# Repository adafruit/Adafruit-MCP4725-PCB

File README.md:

## Adafruit MCP4725 12-Bit DAC Breakout PCB
<a href="http://www.adafruit.com/products/935"><br/>
Click here to purchase one from the Adafruit shop</a>

This breakout board features the easy-to-use MCP4725 12-bit DAC. Control it via I2C and send it the value you want it to output, and the VOUT pin will have it. Great for audio / analog projects, such as when you can't use PWM but need a sine wave or adjustable bias point.

We break out the ADDR/A0 pin so you can connect two of these DACs on one I2C bus, just tie that pin of one high to keep it from conflicting. Also included is a 6-pin header, for use in a breadboard. Works with both 3.3V or 5V logic.

Some nice extras with this chip: for chips that have 3.4Mbps Fast Mode I2C (Arduino's don't) you can update the Vout at ~200 KHz. There's an EEPROM so if you write the output voltage, you can 'store it' so if the device is power cycled it will restore that voltage. The output voltage is rail-to-rail and proportional to the power pin so if you run it from 3.3V, the output range is 0-3.3V. If you run it from 5V the output range is 0-5V.

These are the Eagle CAD files for the Adafruit MCP4725 12-Bit DAC Breakout:
- https://www.adafruit.com/products/935

### License

Adafruit invests time and resources providing this open source design, please support Adafruit and open-source hardware by purchasing products from [Adafruit](https://www.adafruit.com)!

All text above must be included in any redistribution

Designed by Limor Fried/Ladyada for Adafruit Industries.
Creative Commons Attribution/Share-Alike, all text above must be included in any redistribution. 
See license.txt for additional information.

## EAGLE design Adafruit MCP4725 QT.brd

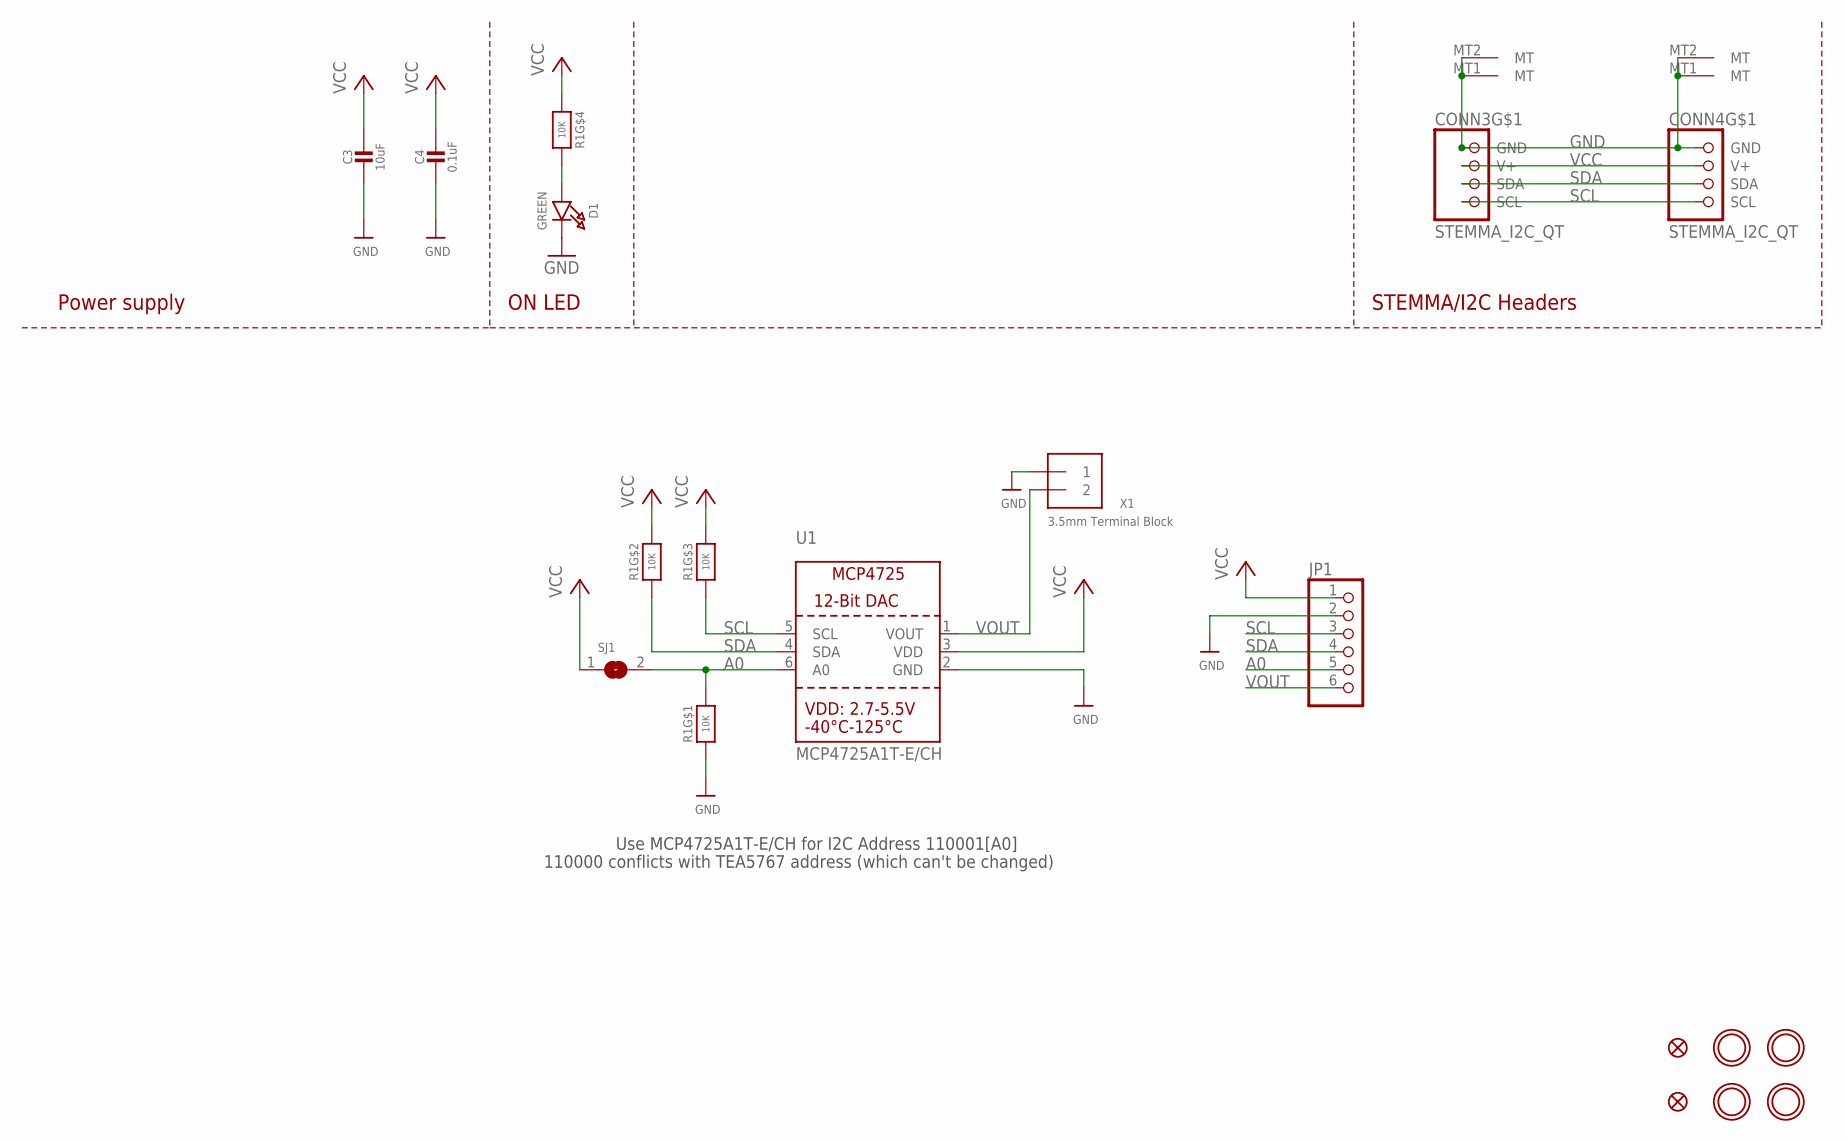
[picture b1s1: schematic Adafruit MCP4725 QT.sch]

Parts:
C3: 10uF; 0805-NO
C4: 0.1uF; 0603-NO
CONN3, CONN4: STEMMA_I2C_QT; JST_SH4
D1: GREEN; CHIPLED_0603_NOOUTLINE
FID3, FID4: FIDUCIAL_1MM
JP1: HEADER-1X670MIL; 1X06_ROUND_70
R1: 10K; RESPACK_4X0603
SJ1: SOLDERJUMPER; SOLDERJUMPER_ARROW_NOPASTE
U1: MCP4725A1T-E/CH; SOT23-6
U$20, U$21, U$25, U$27: MOUNTINGHOLE2.5; MOUNTINGHOLE_2.5_PLATED
X1: 3.5mm Terminal Block; TERMBLOCK_1X2-3.5MM

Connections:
A0: JP1.5, R1.8 (2), SJ1.2, U1.6 (A0)
GND: C3.2, C4.2, CONN3.1 (GND), CONN3.MT1 (MT), CONN3.MT2 (MT), CONN4.1 (GND), CONN4.MT1 (MT), CONN4.MT2 (MT), D1.C, JP1.2, R1.1, U1.2 (GND), X1.1
unnamed: D1.A, R1.5 (2)
SCL: CONN3.4 (SCL), CONN4.4 (SCL), JP1.3, R1.3 (1), U1.5 (SCL)
SDA: CONN3.3 (SDA), CONN4.3 (SDA), JP1.4, R1.2 (1), U1.4 (SDA)
VCC: C3.1, C4.1, CONN3.2 (V+), CONN4.2 (V+), JP1.1, R1.4 (1), R1.6 (2), R1.7 (2), SJ1.1, U1.3 (VDD)
VOUT: JP1.6, U1.1 (VOUT), X1.2

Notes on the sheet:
STEMMA/I2C Headers
ON LED
Power supply
Use MCP4725A1T-E/CH for I2C Address 110001[A0]
110000 conflicts with TEA5767 address (which can't be changed)

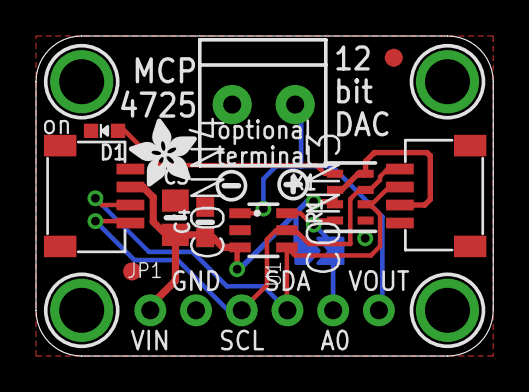
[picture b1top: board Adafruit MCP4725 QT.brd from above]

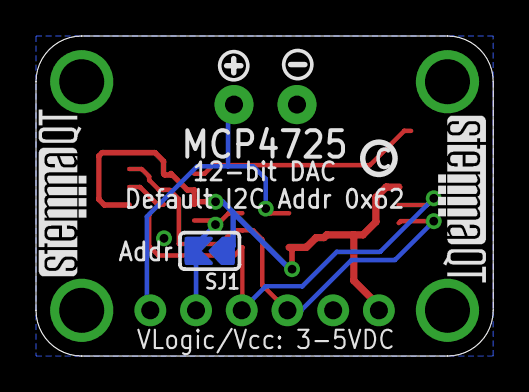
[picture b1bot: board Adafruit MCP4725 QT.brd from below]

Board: 2 copper layers, 25.4 x 17.8 mm, 24 parts (6 on the bottom side), 7 nets.

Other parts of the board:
U$2, U$7: SYMBOL_PLUS
U$4, U$5: SYMBOL_MINUS
U$8: PCBFEAT-REV-040
U$29: ADAFRUIT_3.5MM
U$31, U$32: STEMMAQT

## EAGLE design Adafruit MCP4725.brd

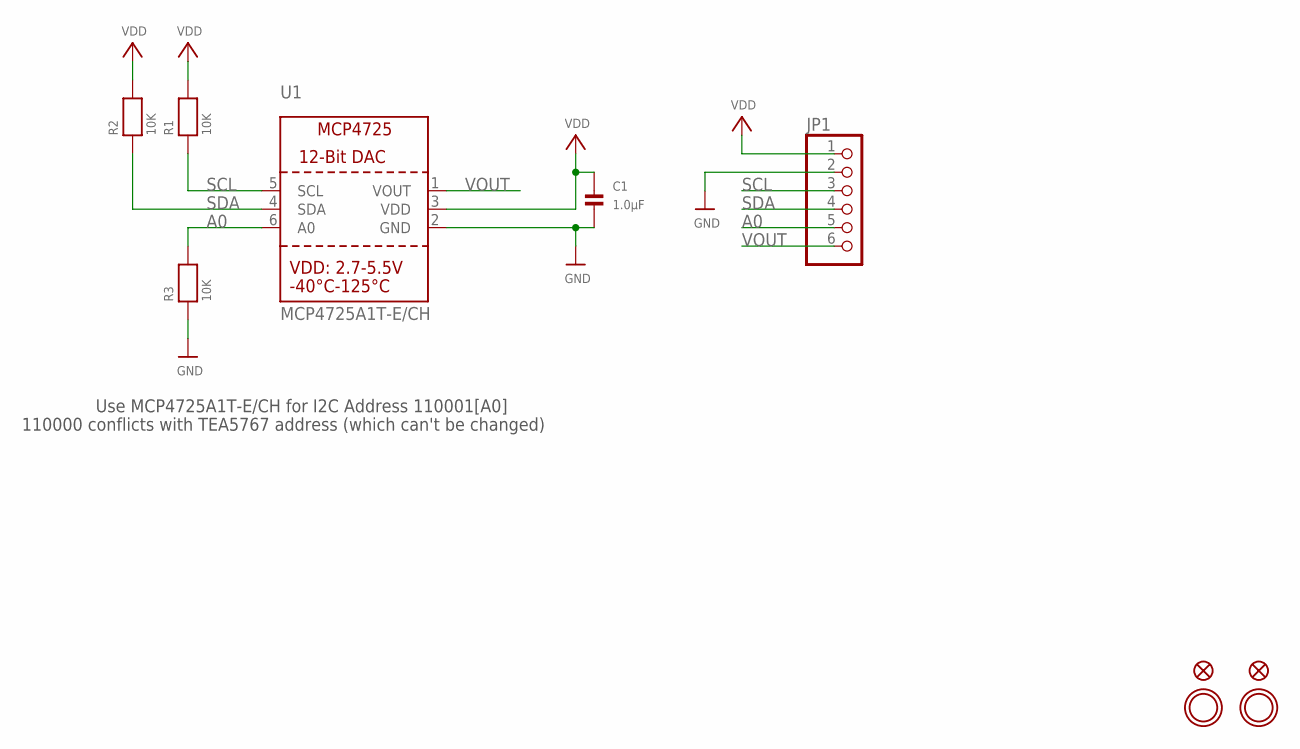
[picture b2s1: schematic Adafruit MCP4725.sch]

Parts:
C1: 1.0µF; 0805
FID1, FID2: FIDUCIAL""; FIDUCIAL_1MM
JP1: HEADER-1X670MIL; 1X06_ROUND_70
R1, R2, R3: 10K; 0805
U1: MCP4725A1T-E/CH; SOT23-6
U$7, U$8: MOUNTINGHOLE2.5; MOUNTINGHOLE_2.5_PLATED

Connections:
A0: JP1.5, R3.2, U1.6 (A0)
GND: C1.2, JP1.2, R3.1, U1.2 (GND)
SCL: JP1.3, R1.1, U1.5 (SCL)
SDA: JP1.4, R2.1, U1.4 (SDA)
VDD: C1.1, JP1.1, R1.2, R2.2, U1.3 (VDD)
VOUT: JP1.6, U1.1 (VOUT)

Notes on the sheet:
Use MCP4725A1T-E/CH for I2C Address 110001[A0]
110000 conflicts with TEA5767 address (which can't be changed)

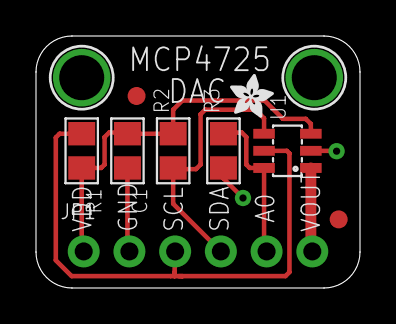
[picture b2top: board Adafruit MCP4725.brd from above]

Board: 2 copper layers, 18.0 x 14.0 mm, 11 parts (0 on the bottom side), 6 nets.

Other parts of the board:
U$11: ADAFRUIT_2.5MM

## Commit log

2016-02-02 init
2022-02-09 Rename Adafruit MCP4725.brd to Adafruit MCP4725 Original.brd
2022-02-09 Rename Adafruit MCP4725.sch to Adafruit MCP4725 Original.sch
2022-02-09 Add QT board files.
